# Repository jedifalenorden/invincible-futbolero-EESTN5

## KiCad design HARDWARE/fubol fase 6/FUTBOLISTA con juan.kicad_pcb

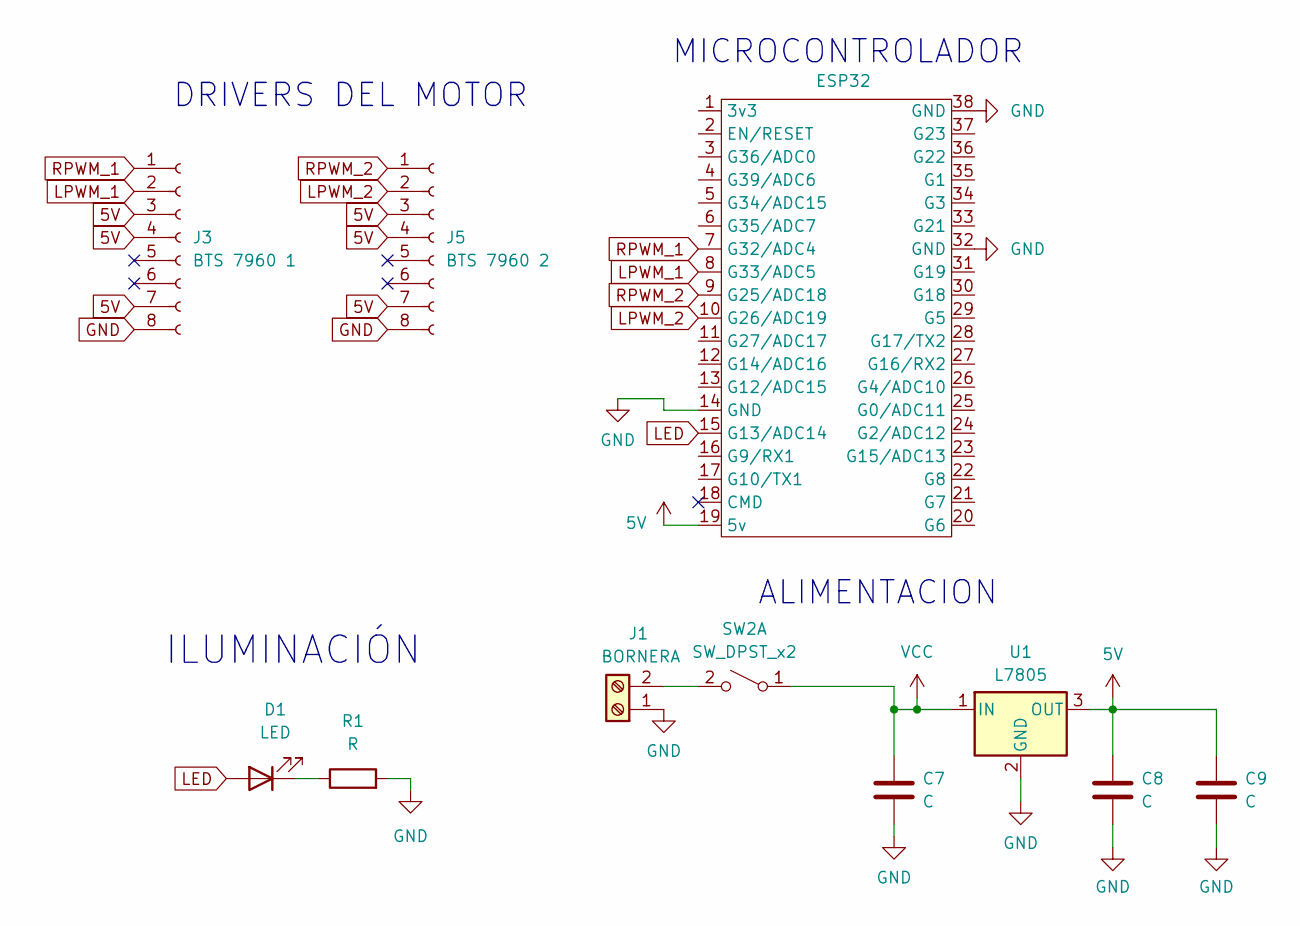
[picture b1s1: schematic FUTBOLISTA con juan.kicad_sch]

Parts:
C7, C8: C; C_0805_2012Metric_Pad1.18x1.45mm_HandSolder
C9: C; CP_Radial_D6.3mm_P2.50mm
D1: LED; led_5mm_red
ESP32: esp32 38 pin
J1: BORNERA; AMASS_XT30U-F_1x02_P5.0mm_Vertical
J3: BTS 7960 1; IDC-Header_2x04_P2.54mm_Vertical
J5: BTS 7960 2; IDC-Header_2x04_P2.54mm_Vertical
R1: R; R_0805_2012Metric_Pad1.20x1.40mm_HandSolder
SW2: SW_DPST_x2; SW_PUSH_1P1T_6x3.5mm_H5.0_APEM_MJTP1250
U1: L7805; TO-263-3_TabPin2

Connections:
5V: C8.1, C9.1, ESP32.19 (5v), J3.3, J3.4, J3.7, J5.3, J5.4, J5.7, U1.3 (OUT)
GND: C7.2, C8.2, C9.2, ESP32.14 (GND), ESP32.32 (GND), ESP32.38 (GND), J1.1, J3.8, J5.8, R1.2, U1.2 (GND)
LED: D1.2 (A), ESP32.15 (G13/ADC14)
LPWM_1: ESP32.8 (G33/ADC5), J3.2
LPWM_2: ESP32.10 (G26/ADC19), J5.2
unnamed: D1.1 (K), R1.1
unnamed: J1.2, SW2.2 (B)
RPWM_1: ESP32.7 (G32/ADC4), J3.1
RPWM_2: ESP32.9 (G25/ADC18), J5.1
VCC: C7.1, SW2.1 (A), U1.1 (IN)

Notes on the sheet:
MICROCONTROLADOR
ALIMENTACION
ILUMINACIÓN
DRIVERS DEL MOTOR

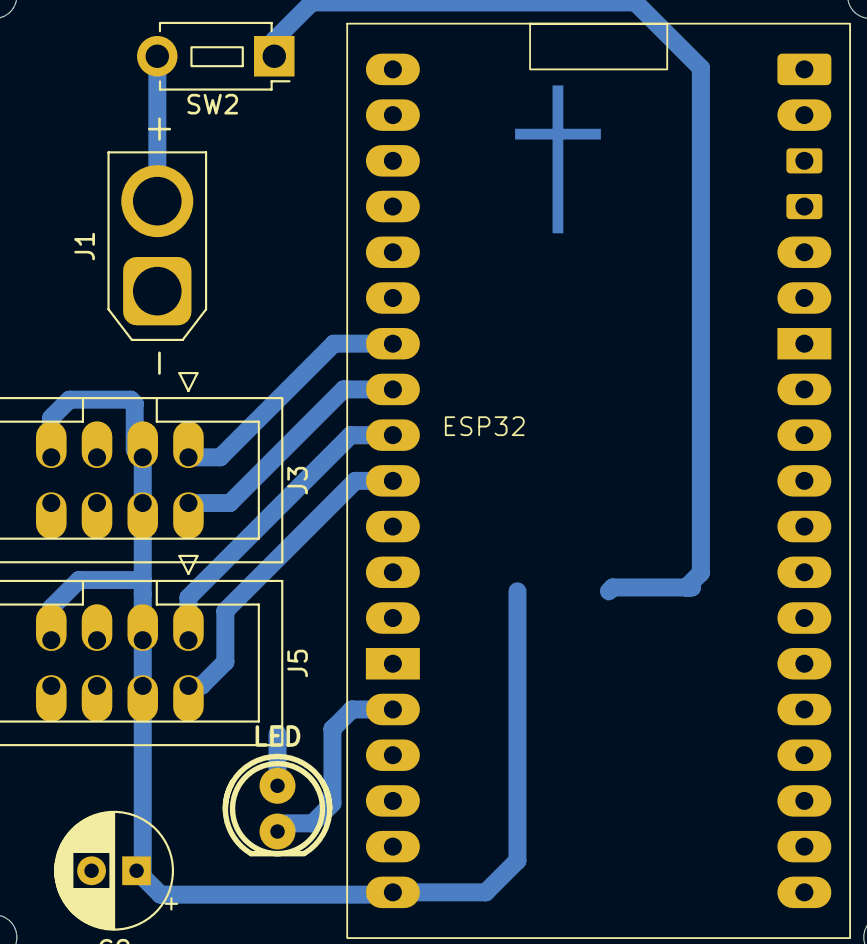
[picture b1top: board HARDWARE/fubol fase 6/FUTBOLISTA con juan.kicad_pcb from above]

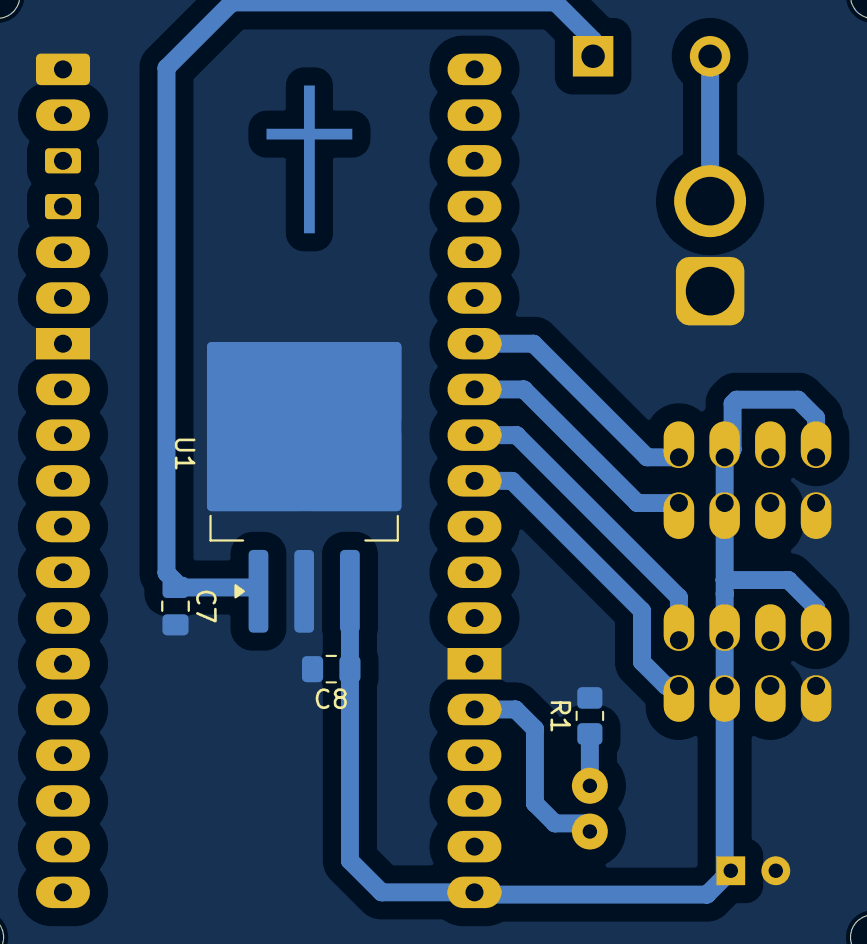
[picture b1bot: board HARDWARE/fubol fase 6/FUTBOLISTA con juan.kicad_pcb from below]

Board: 2 copper layers, 11 parts (4 on the bottom side), 10 nets.

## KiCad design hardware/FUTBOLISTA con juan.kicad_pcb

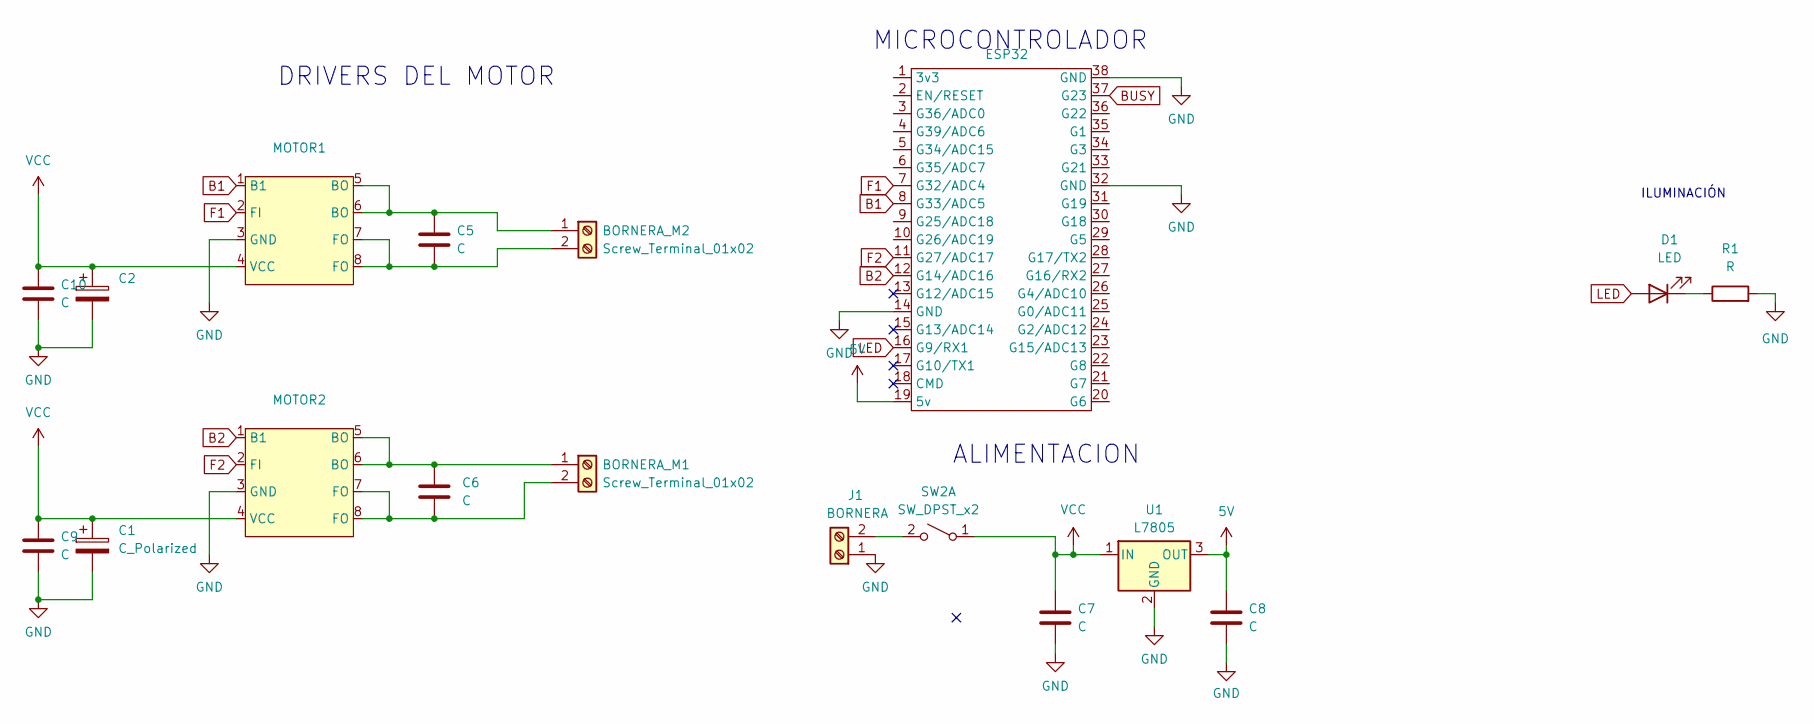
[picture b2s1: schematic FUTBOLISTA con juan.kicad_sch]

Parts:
BORNERA_M1, BORNERA_M2: Screw_Terminal_01x02; TerminalBlock_Phoenix_MKDS-1,5-2-5.08_1x02_P5.08mm_Horizont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
C1, C2: C_Polarized; CAP_ELEC_5x11mm
C5, C6, C7, C8, C9, C10: C; C_0805_2012Metric_Pad1.18x1.45mm_HandSolder
D1: LED; led_5mm_red
ESP32: esp32 38 pin
J1: BORNERA; AMASS_XT60-F_1x02_P7.20mm_Vertical
MOTOR1, MOTOR2: DIP-8_W7.62mm
R1: R; R_0805_2012Metric_Pad1.20x1.40mm_HandSolder
SW2: SW_DPST_x2; SW_PUSH_1P1T_6x3.5mm_H5.0_APEM_MJTP1250
U1: L7805; TO-263-3_TabPin2

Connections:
5V: C8.1, ESP32.19 (5v), U1.3 (OUT)
B1: ESP32.8 (G33/ADC5), MOTOR1.1 (B1)
B2: ESP32.12 (G14/ADC16), MOTOR2.1 (B1)
BUSY: ESP32.37 (G23)
F1: ESP32.7 (G32/ADC4), MOTOR1.2 (FI)
F2: ESP32.11 (G27/ADC17), MOTOR2.2 (FI)
GND: C1.2, C2.2, C7.2, C8.2, C9.2, C10.2, ESP32.14 (GND), ESP32.32 (GND), ESP32.38 (GND), J1.1, MOTOR1.3 (GND), MOTOR2.3 (GND), R1.2, U1.2 (GND)
LED: D1.2 (A), ESP32.16 (G9/RX1)
unnamed: BORNERA_M1.1, C6.2, MOTOR2.5 (BO), MOTOR2.6 (BO)
unnamed: BORNERA_M1.2, C6.1, MOTOR2.7 (FO), MOTOR2.8 (FO)
unnamed: BORNERA_M2.1, C5.1, MOTOR1.5 (BO), MOTOR1.6 (BO)
unnamed: BORNERA_M2.2, C5.2, MOTOR1.7 (FO), MOTOR1.8 (FO)
unnamed: D1.1 (K), R1.1
unnamed: J1.2, SW2.2 (B)
VCC: C1.1, C2.1, C7.1, C9.1, C10.1, MOTOR1.4 (VCC), MOTOR2.4 (VCC), SW2.1 (A), U1.1 (IN)

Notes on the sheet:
MICROCONTROLADOR
ALIMENTACION
ILUMINACIÓN
DRIVERS DEL MOTOR

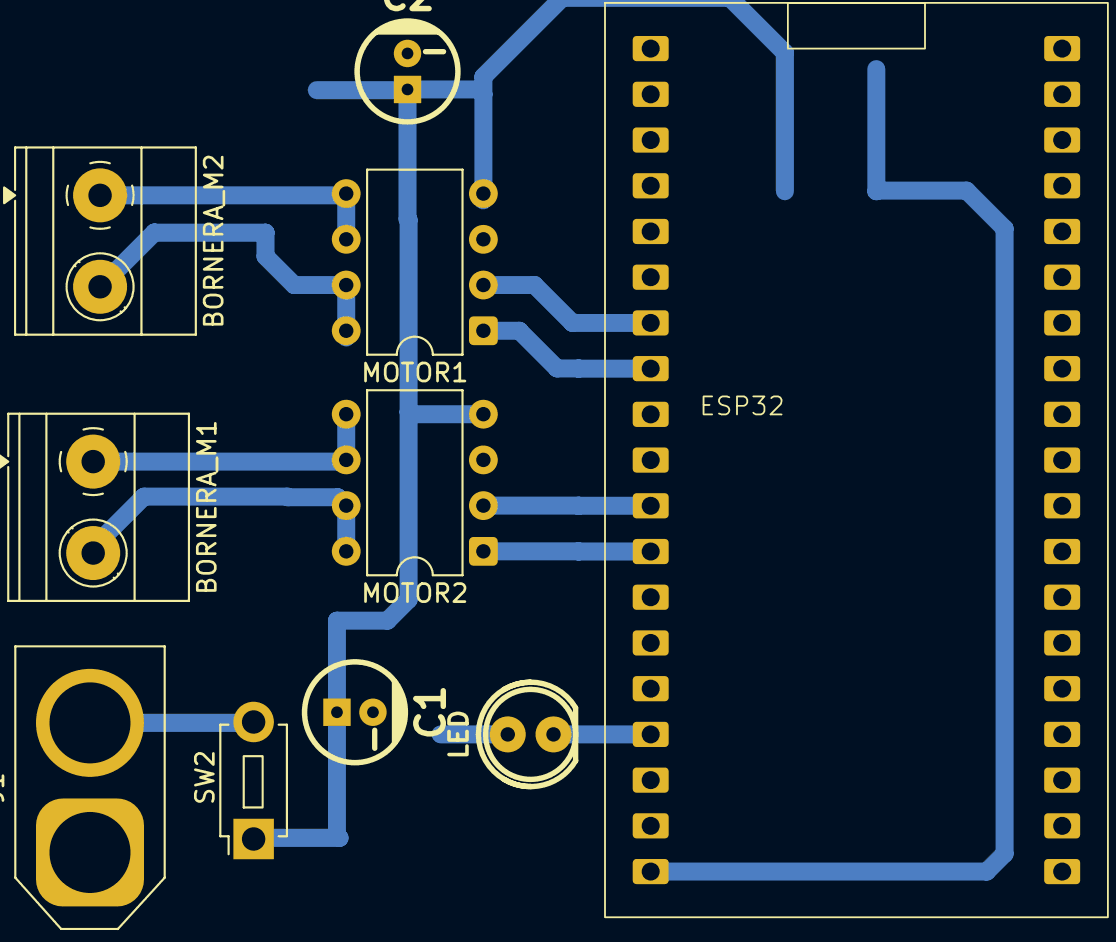
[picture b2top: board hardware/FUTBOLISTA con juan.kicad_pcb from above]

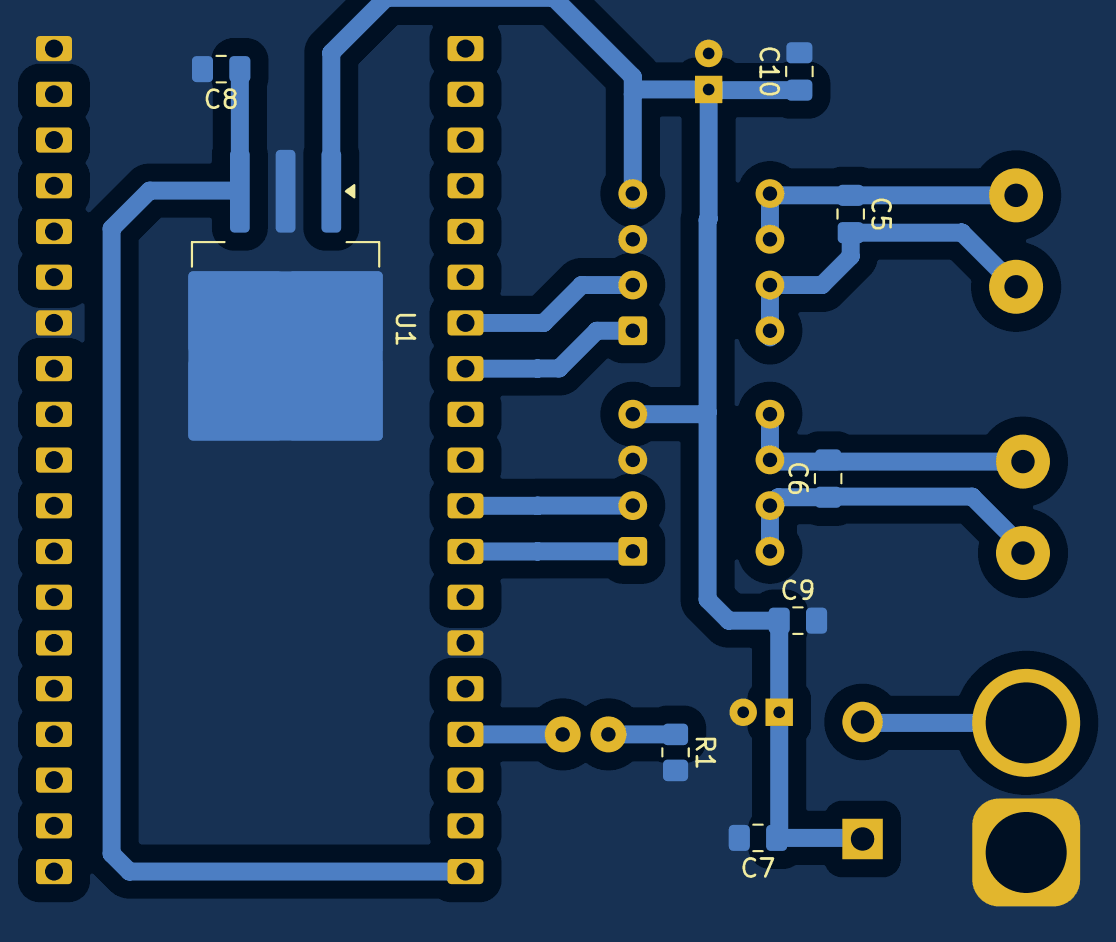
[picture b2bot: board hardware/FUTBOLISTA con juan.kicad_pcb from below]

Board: 2 copper layers, 18 parts (8 on the bottom side), 14 nets.

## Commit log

2026-04-29 Create za
2026-04-29 Add new file 'a' with initial content
2026-04-29 Create ad
2026-04-29 Create adsa
2026-05-06 Add initial content to hardware file
2026-05-11 Create FASE 3 FUBOL
2026-05-11 Create fubol fase 3
2026-05-18 Create dasd
2026-05-27 Create jh
2026-05-27 Create sad
2026-05-27 Create afs
2026-06-02 Create software
2026-06-29 Add new file ads with initial content
